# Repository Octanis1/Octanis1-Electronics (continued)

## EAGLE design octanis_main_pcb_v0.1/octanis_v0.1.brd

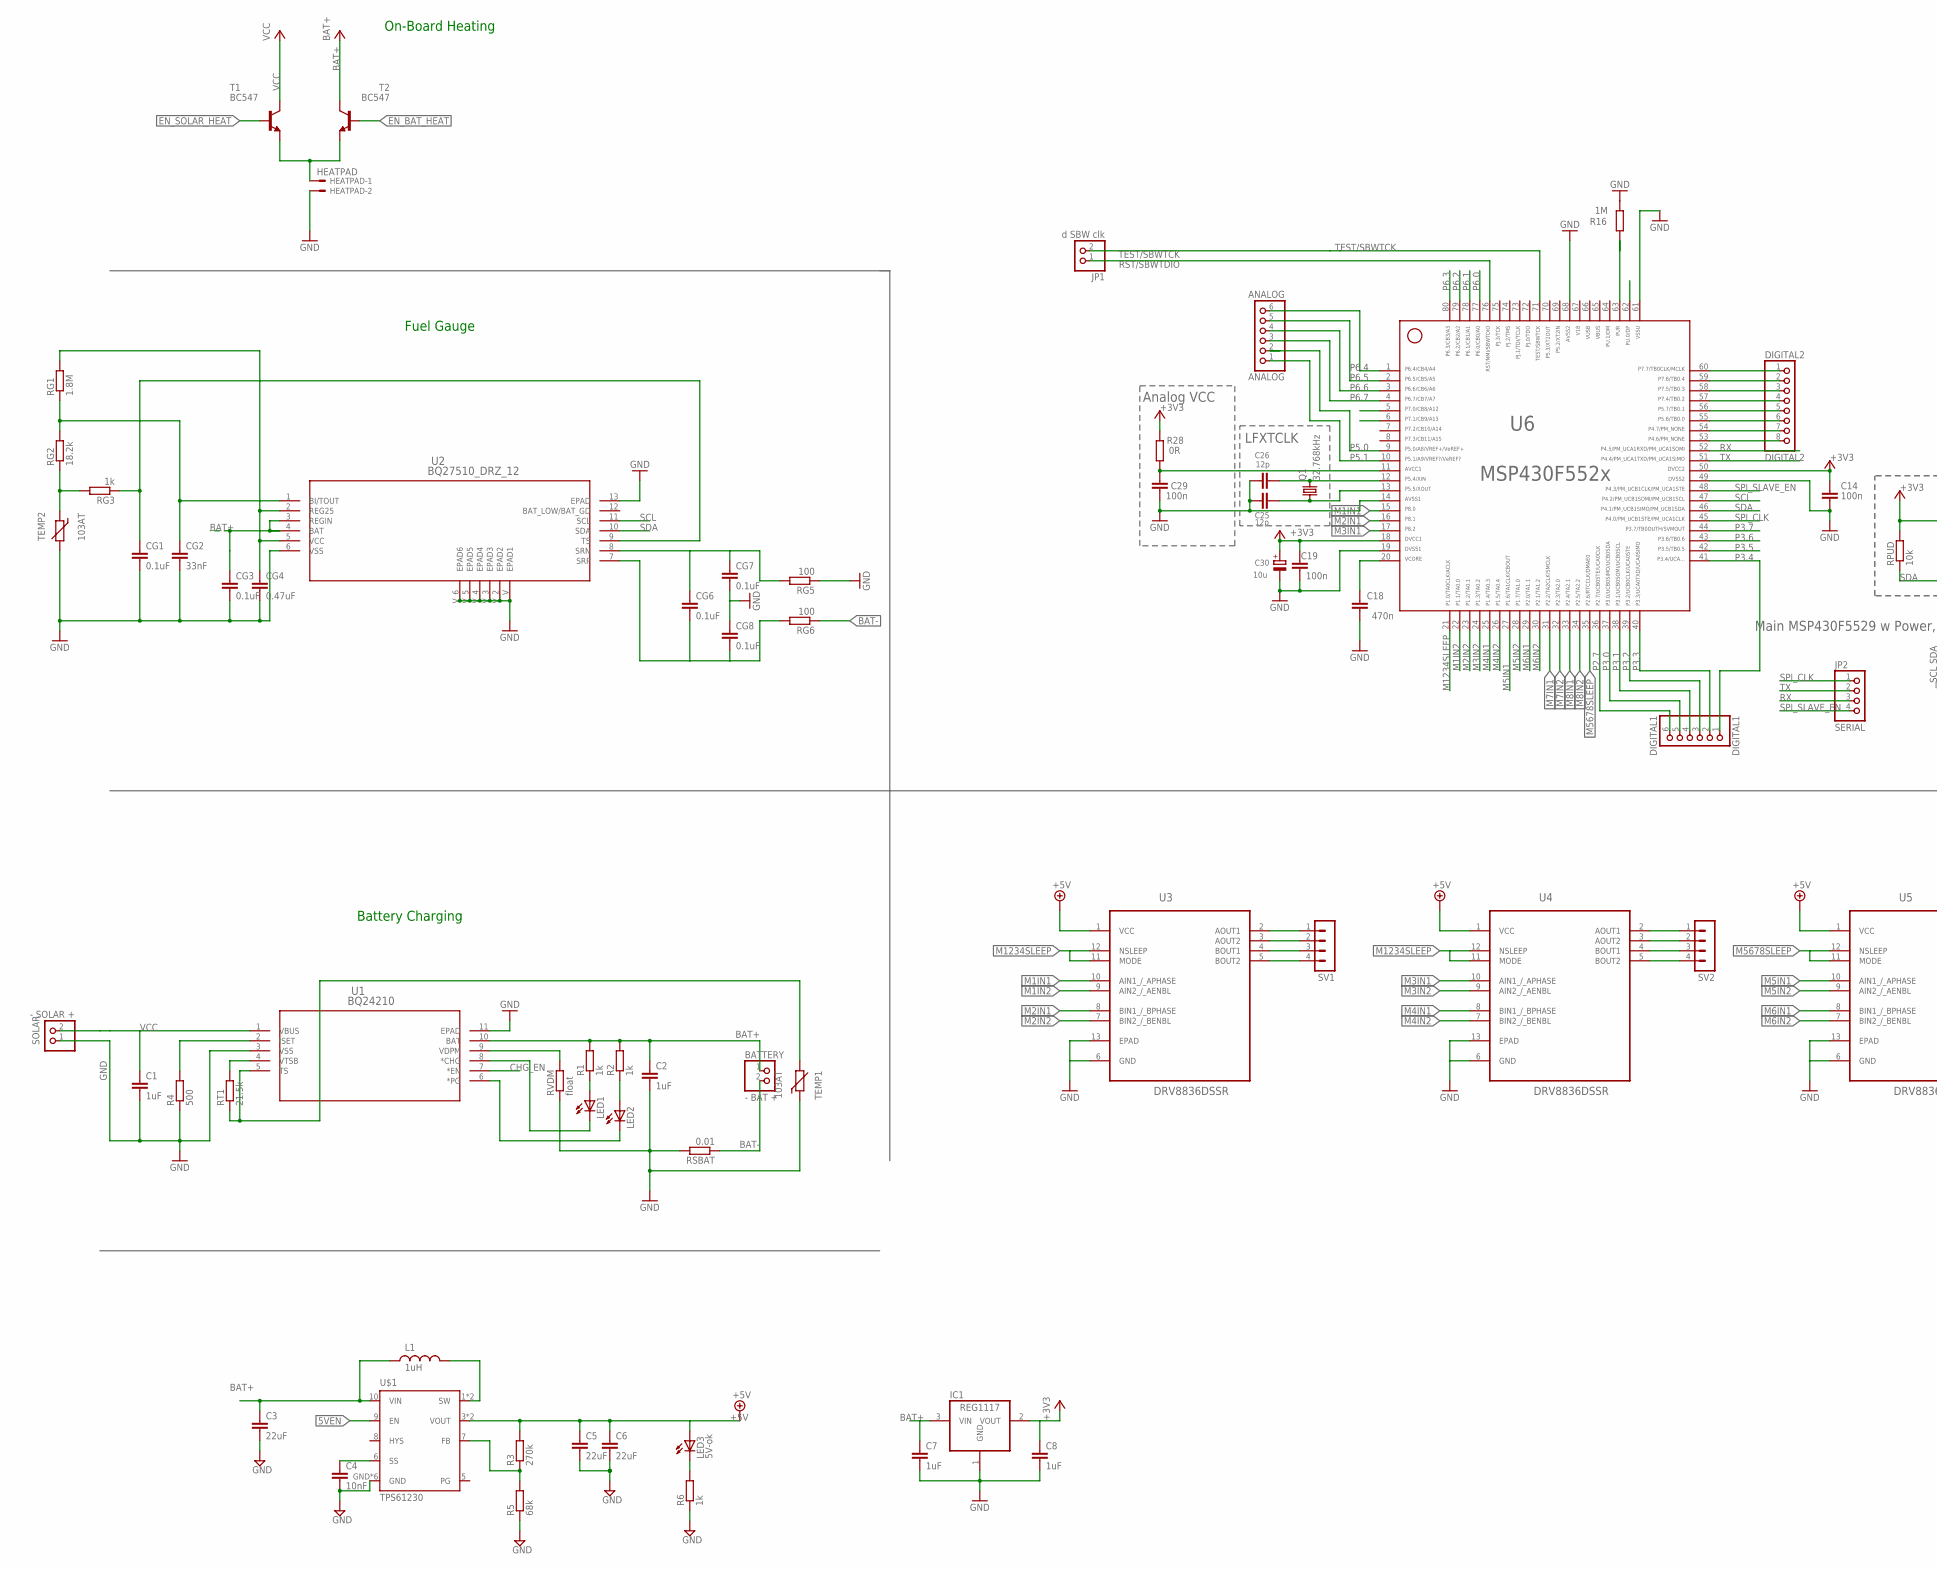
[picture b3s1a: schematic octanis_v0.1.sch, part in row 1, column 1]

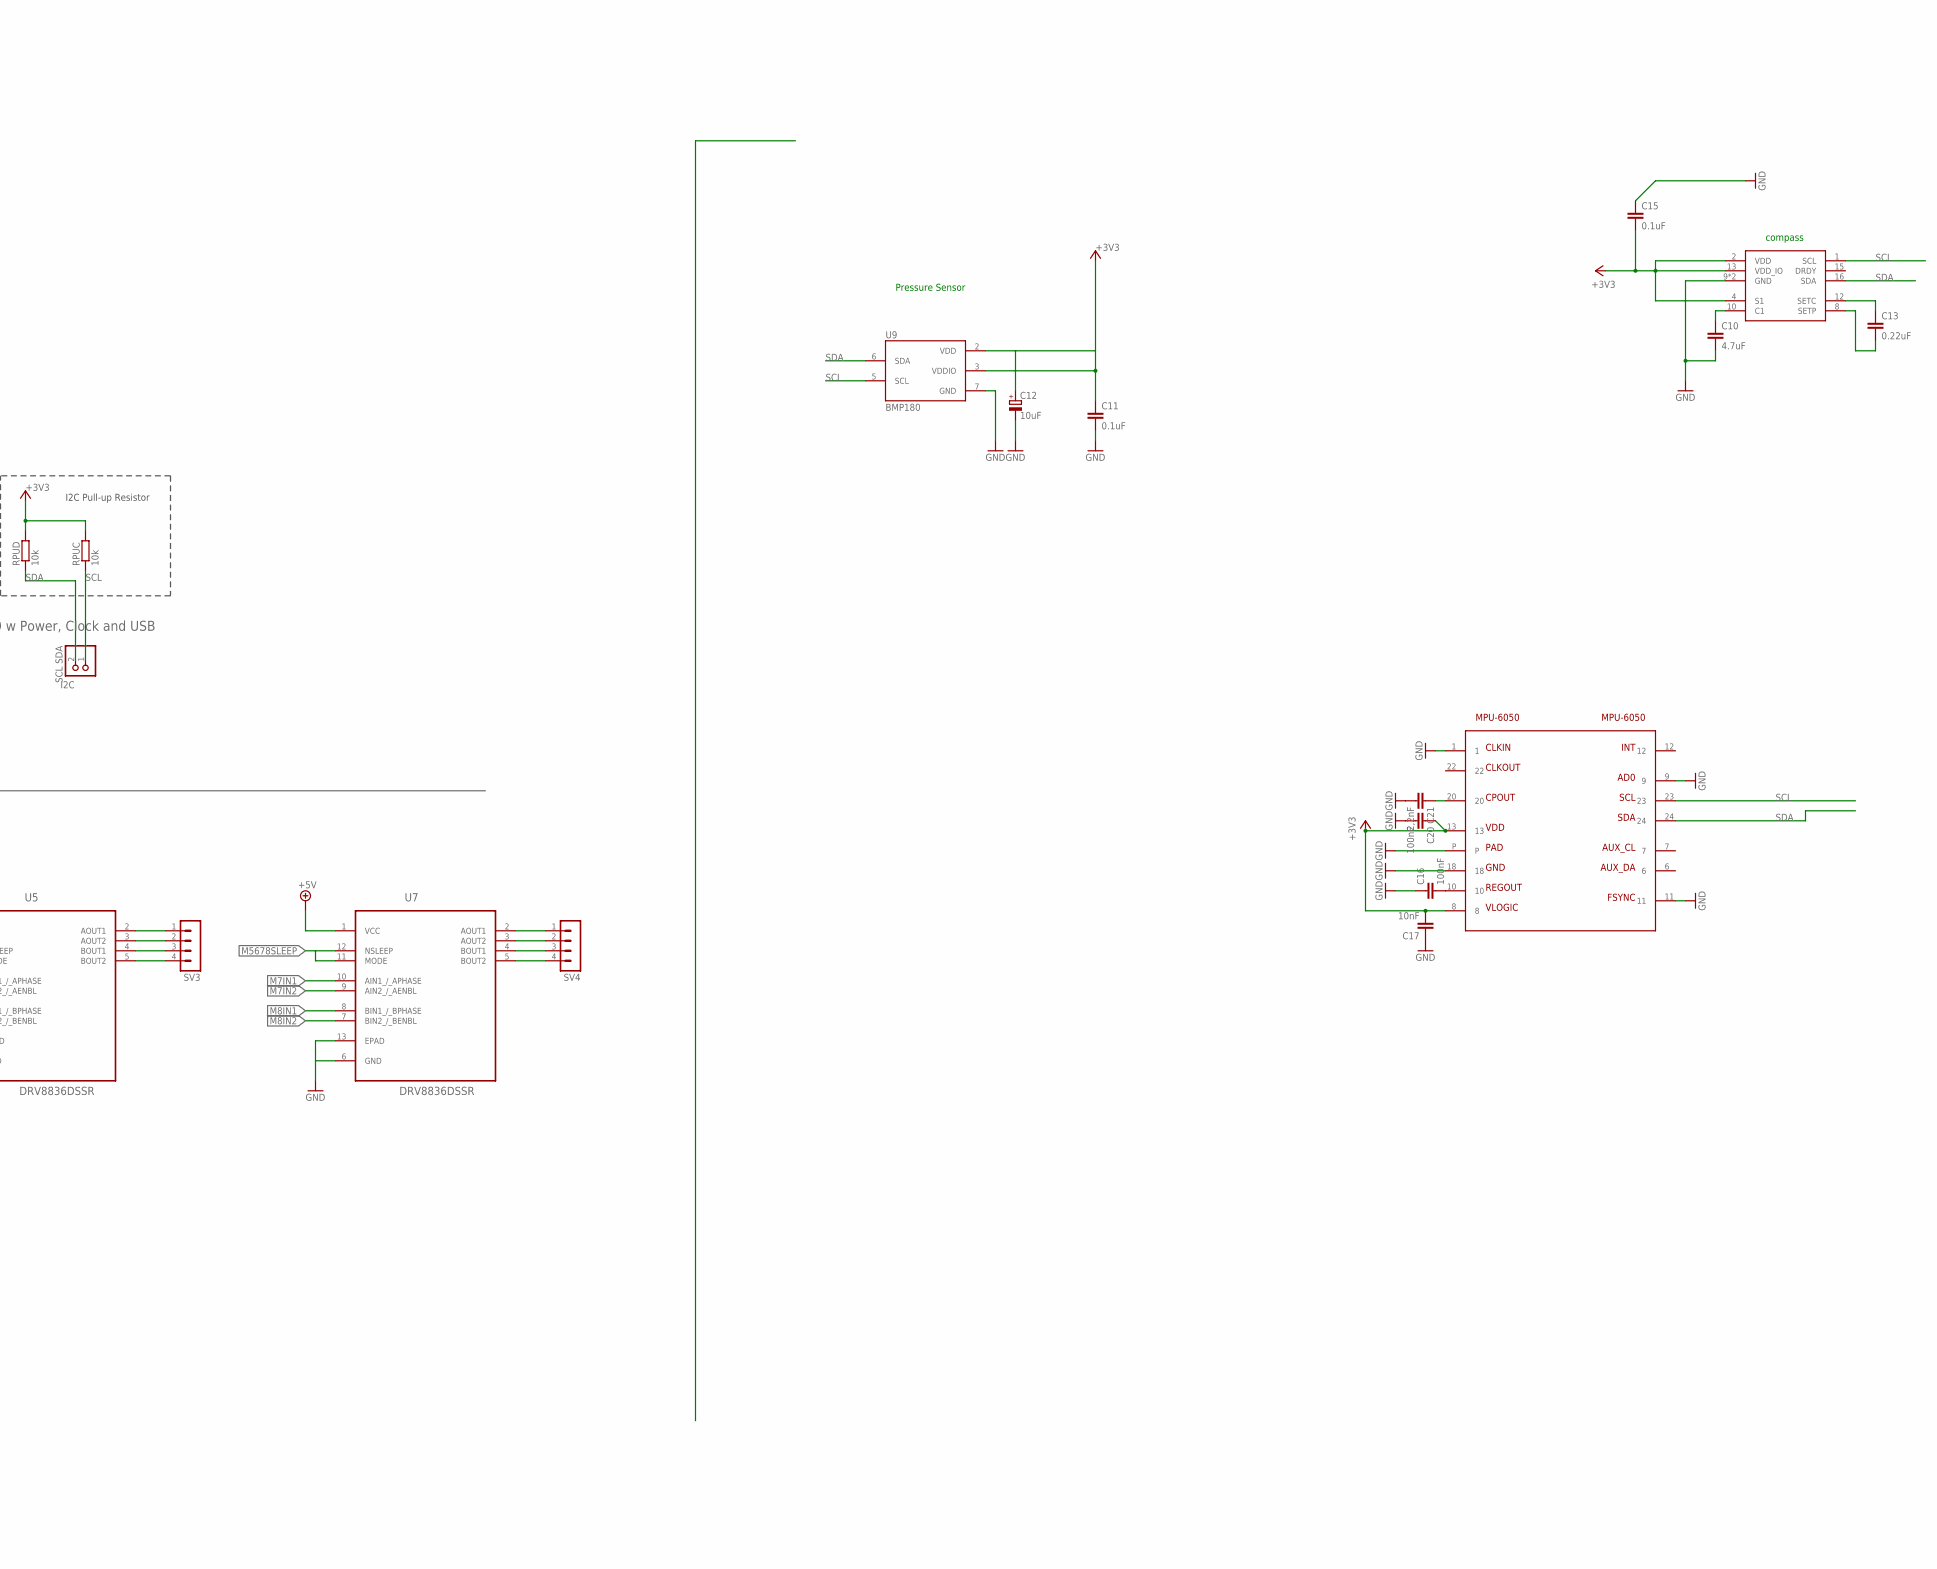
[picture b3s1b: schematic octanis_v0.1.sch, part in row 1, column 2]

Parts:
ANALOG: ANALOG; 1X06
BATTERY: - BAT +; 1X02
C1, C2: 1uF; C1206
C3, C5, C6: 22uF; C0603
C4, C17: 10nF; C0603
C7, C8: 1uF; C0603
C10: 4.7uF; C0603
C11, C15: 0.1uF; C0603
C12: 10uF; A/3216-18R
C13: 0.22uF; C0603
C14, C19, C29: 100n; C0603
C16, C20: 100nF; C0603
C18: 470n; C0603
C21: 2,2nF; C0603
C25, C26: 12p; C0603
C30: 10u; A/3216-18R
CG1, CG3, CG6, CG7, CG8: 0.1uF; C0603
CG2: 33nF; C0603
CG4: 0.47uF; C0603
COMPASS: HMC5883L; LPCC16
DIGITAL1: DIGITAL1; 1X06
DIGITAL2: DIGITAL2; 1X08
HEATPAD: HEATPAD; 22-23-2021
I2C: SCL SDA; 1X02
IC1: REG1117; SOT223
JP1: d SBW clk; 1X02
JP2: SERIAL; 1X04
L1: 1uH; XFL4020
LED1, LED2: LEDCHIP-LED0603; CHIP-LED0603
LED3: 5V-ok; CHIPLED_0603
MPU-6050: MPU-6050; QFN24
Q1: 32.768kHz; FC-12M
R1, R2, R6: 1k; R0603
R3: 270k; R0603
R4: 500; R1206
R5: 68k; R0603
R16: 1M; R0603
R28: 0R; R0603
RG1: 1.8M; R0603
RG2: 18.2k; R0603
RG3: 1k; R0603
RG5, RG6: 100; R0603
RPUC: 10k; R0603
RPUD: 10k; R0603
RSBAT: 0.01; R1206
RT1: 21.5k; R1206
RVDM: float; R1206
SOLAR: - SOLAR +; 1X02
SV1, SV2, SV3, SV4: MA04-1
T1, T2: BC547; TO92
TEMP1, TEMP2: 103AT; RS-2,5
U1: BQ24210; DQC10_P84X2P4
U2: BQ27510_DRZ_12; DRZ12_1P95X2P45
U3, U4, U5, U7: DRV8836DSSR; SON50P200X300X80-13N
U6: MSP430F5529IPNR; PN80
U9: BMP180
U$1: TPS61230; DRC-S-PVSON-N11

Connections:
5VEN: U6.6, U$1.9 (EN)
65: U6.65
66: U6.66
67: U6.67
+3V3: C8.1, C11.1, C12.+, C14.1, C15.2, C17.2, C19.2, C20.1, C30.+, COMPASS.2 (VDD), COMPASS.4 (S1), COMPASS.13 (VDD_IO), IC1.2 (VOUT), MPU-6050.8, MPU-6050.13, R28.2, RPUC.2, RPUD.2, U6.18, U6.50, U9.2 (VDD), U9.3 (VDDIO)
+5V: C5.1, C6.1, LED3.A, R3.2, U3.1 (VCC), U4.1 (VCC), U5.1 (VCC), U7.1 (VCC), U$1.3 (VOUT), U$1.4 (VOUT)
AVCC: C29.1, R28.1, U6.11
BAT+: BATTERY.1, C2.1, C3.1, C7.1, CG3.1, IC1.3 (VIN), L1.P$1 (1), R1.2, R2.2, T2.3 (C), U1.10 (BAT), U2.3 (REGIN), U2.4 (BAT), U$1.10 (VIN)
BAT-: BATTERY.2, RG6.1, RSBAT.1
CHG_EN: U1.7 (*EN), U6.5
EN_BAT_HEAT: T2.2 (B)
EN_SOLAR_HEAT: T1.2 (B)
GND: C1.2, C2.2, C3.2, C4.2, C5.2, C6.2, C7.2, C8.2, C10.2, C11.2, C12.-, C14.2, C15.1, C16.1, C17.1, C18.1, C19.1, C20.2, C21.2, C25.1, C26.1, C29.2, C30.-, CG1.2, CG2.2, CG3.2, CG4.2, CG7.2, CG8.1, COMPASS.9 (GND), COMPASS.11 (GND), HEATPAD.2, IC1.1 (GND), MPU-6050.1, MPU-6050.9, MPU-6050.11, MPU-6050.18, MPU-6050.P, R4.1, R5.1, R6.1, R16.1, RG5.1, RSBAT.2, RVDM.1, SOLAR.1, TEMP1.1, TEMP2.2, U1.3 (VSS), U1.11 (EPAD), U2.6 (VSS), U2.13 (EPAD), U2.V (EPAD1), U2.V_2 (EPAD2), U2.V_3 (EPAD3), U2.V_4 (EPAD4), U2.V_5 (EPAD5), U2.V_6 (EPAD6), U3.6 (GND), U3.13 (EPAD), U4.6 (GND), U4.13 (EPAD), U5.6 (GND), U5.13 (EPAD), U6.14, U6.19, U6.49, U6.61, U6.68, U7.6 (GND), U7.13 (EPAD), U9.7 (GND), U$1.GND, U$1.GND@1 (GND), U$1.GND@2 (GND), U$1.GND@3 (GND), U$1.GND@4 (GND), U$1.GND@5 (GND)
IND: L1.P$2 (2), U$1.1 (SW), U$1.2 (SW)
M1IN1: U3.10 (AIN1_/_APHASE), U6.15
M1IN2: U3.9 (AIN2_/_AENBL), U6.22
M2IN1: U3.8 (BIN1_/_BPHASE), U6.16
M2IN2: U3.7 (BIN2_/_BENBL), U6.23
M3IN1: U4.10 (AIN1_/_APHASE), U6.17
M3IN2: U4.9 (AIN2_/_AENBL), U6.24
M4IN1: U4.8 (BIN1_/_BPHASE), U6.25
M4IN2: U4.7 (BIN2_/_BENBL), U6.26
M5IN1: U5.10 (AIN1_/_APHASE), U6.27
M5IN2: U5.9 (AIN2_/_AENBL), U6.28
M6IN1: U5.8 (BIN1_/_BPHASE), U6.29
M6IN2: U5.7 (BIN2_/_BENBL), U6.30
M7IN1: U6.31, U7.10 (AIN1_/_APHASE)
M7IN2: U6.32, U7.9 (AIN2_/_AENBL)
M8IN1: U6.33, U7.8 (BIN1_/_BPHASE)
M8IN2: U6.34, U7.7 (BIN2_/_BENBL)
M1234SLEEP: U3.11 (MODE), U3.12 (NSLEEP), U4.11 (MODE), U4.12 (NSLEEP), U6.21
M5678SLEEP: U5.11 (MODE), U5.12 (NSLEEP), U6.35, U7.11 (MODE), U7.12 (NSLEEP)
unnamed: CG2.1, RG1.1, RG2.2, U2.1 (BI/TOUT)
unnamed: LED1.A, R1.1
unnamed: LED2.A, R2.1
unnamed: LED1.C, U1.8 (*CHG)
unnamed: LED2.C, U1.6 (*PG)
unnamed: RVDM.2, U1.9 (VDPM)
unnamed: RT1.1, TEMP1.2, U1.5 (TS)
unnamed: RT1.2, U1.4 (VTSB)
unnamed: R4.2, U1.2 (ISET)
unnamed: SV2.1, U4.2 (AOUT1)
unnamed: DIGITAL2.1, U6.60
unnamed: DIGITAL2.2, U6.59
unnamed: C10.1, COMPASS.10 (C1)
unnamed: C16.2, MPU-6050.10
unnamed: C21.1, MPU-6050.20
unnamed: DIGITAL2.3, U6.58
unnamed: DIGITAL2.4, U6.57
unnamed: DIGITAL2.5, U6.56
unnamed: DIGITAL2.6, U6.55
unnamed: DIGITAL2.7, U6.54
unnamed: C13.2, COMPASS.8 (SETP)
unnamed: DIGITAL2.8, U6.53
unnamed: C13.1, COMPASS.12 (SETC)
unnamed: RG2.1, RG3.2, TEMP2.1
unnamed: CG1.1, RG3.1, U2.9 (TS)
unnamed: CG4.1, RG1.2, U2.2 (REG25), U2.5 (VCC)
unnamed: CG6.1, CG7.1, RG5.2, U2.8 (SRN)
unnamed: HEATPAD.1, T1.1 (E), T2.1 (E)
unnamed: CG6.2, CG8.2, RG6.2, U2.7 (SRP)
unnamed: SV2.2, U4.3 (AOUT2)
unnamed: SV2.3, U4.4 (BOUT1)
unnamed: SV2.4, U4.5 (BOUT2)
unnamed: C4.1, U$1.6 (SS)
unnamed: R3.1, R5.2, U$1.7 (FB)
unnamed: LED3.C, R6.2
unnamed: SV3.1, U5.2 (AOUT1)
unnamed: SV3.2, U5.3 (AOUT2)
unnamed: SV3.3, U5.4 (BOUT1)
unnamed: SV3.4, U5.5 (BOUT2)
unnamed: SV1.1, U3.2 (AOUT1)
unnamed: SV1.2, U3.3 (AOUT2)
unnamed: SV1.3, U3.4 (BOUT1)
unnamed: SV1.4, U3.5 (BOUT2)
unnamed: SV4.1, U7.2 (AOUT1)
unnamed: SV4.2, U7.3 (AOUT2)
unnamed: SV4.3, U7.4 (BOUT1)
unnamed: SV4.4, U7.5 (BOUT2)
P2.7: DIGITAL1.6, U6.36
P3.0: DIGITAL1.5, U6.37
P3.1: DIGITAL1.4, U6.38
P3.2: DIGITAL1.3, U6.39
P3.3: DIGITAL1.2, U6.40
P3.4: DIGITAL1.1, U6.41
P3.5: U6.42
P3.6: U6.43
P3.7: U6.44
P5.0: ANALOG.2, U6.9
P5.1: ANALOG.1, U6.10
P5.4/XIN: C26.2, Q1.2, U6.12
P5.5/XOUT: C25.2, Q1.1, U6.13
P6.0: U6.77
P6.1: U6.78
P6.2: U6.79
P6.3: U6.80
P6.4: ANALOG.6, U6.1
P6.5: ANALOG.5, U6.2
P6.6: ANALOG.4, U6.3
P6.7: ANALOG.3, U6.4
PG: U$1.5 (PG)
RST/SBWTDIO: JP1.1, U6.76
RX: JP2.3, U6.52
SCL: COMPASS.1 (SCL), I2C.1, MPU-6050.23, RPUC.1, U2.11 (SCL), U6.47, U9.5 (SCL)
SDA: COMPASS.16 (SDA), I2C.2, MPU-6050.24, RPUD.1, U2.10 (SDA), U6.46, U9.6 (SDA)
SPI_CLK: JP2.1, U6.45
SPI_SLAVE_EN: JP2.4, U6.48
TARGET_DP: U6.62
TARGET_PUR: R16.2, U6.63
TEST/SBWTCK: JP1.2, U6.71
TX: JP2.2, U6.51
VCC: C1.1, SOLAR.2, T1.3 (C), U1.1 (VBUS)
VCORE: C18.2, U6.20

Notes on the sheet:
Battery Charging
Fuel Gauge
LFXTCLK
Main MSP430F5529 w Power, Clock and USB
Analog VCC
I2C Pull-up Resistor
On-Board Heating
Pressure Sensor
compass

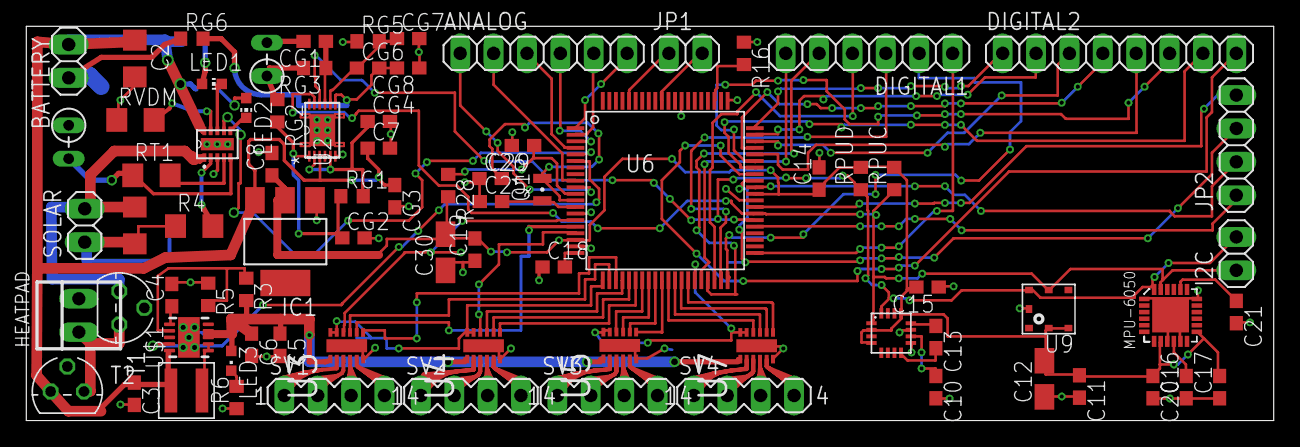
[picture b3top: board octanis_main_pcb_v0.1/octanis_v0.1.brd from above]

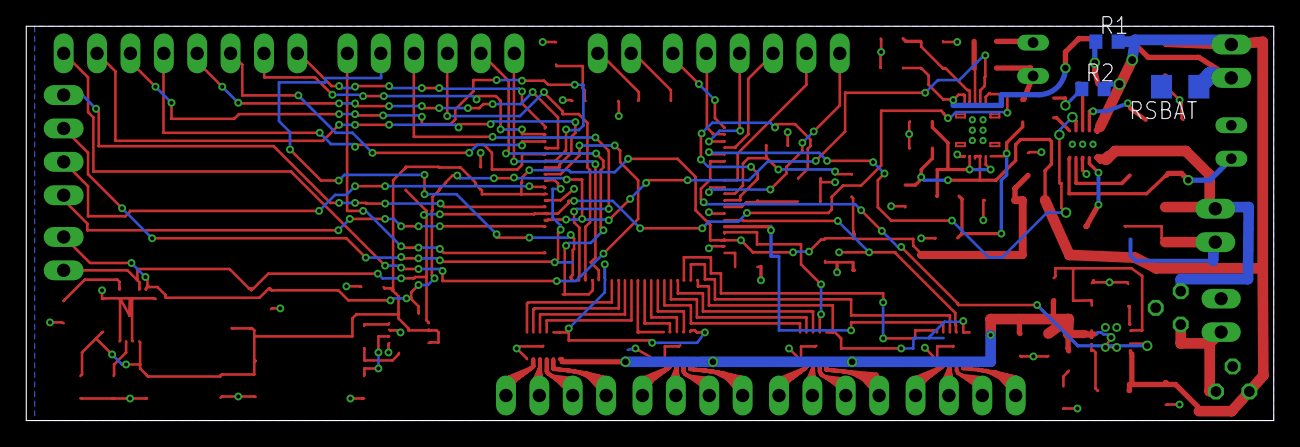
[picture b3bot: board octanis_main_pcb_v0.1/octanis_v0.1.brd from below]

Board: 4 copper layers, 94.9 x 30.0 mm, 83 parts (3 on the bottom side), 99 nets.

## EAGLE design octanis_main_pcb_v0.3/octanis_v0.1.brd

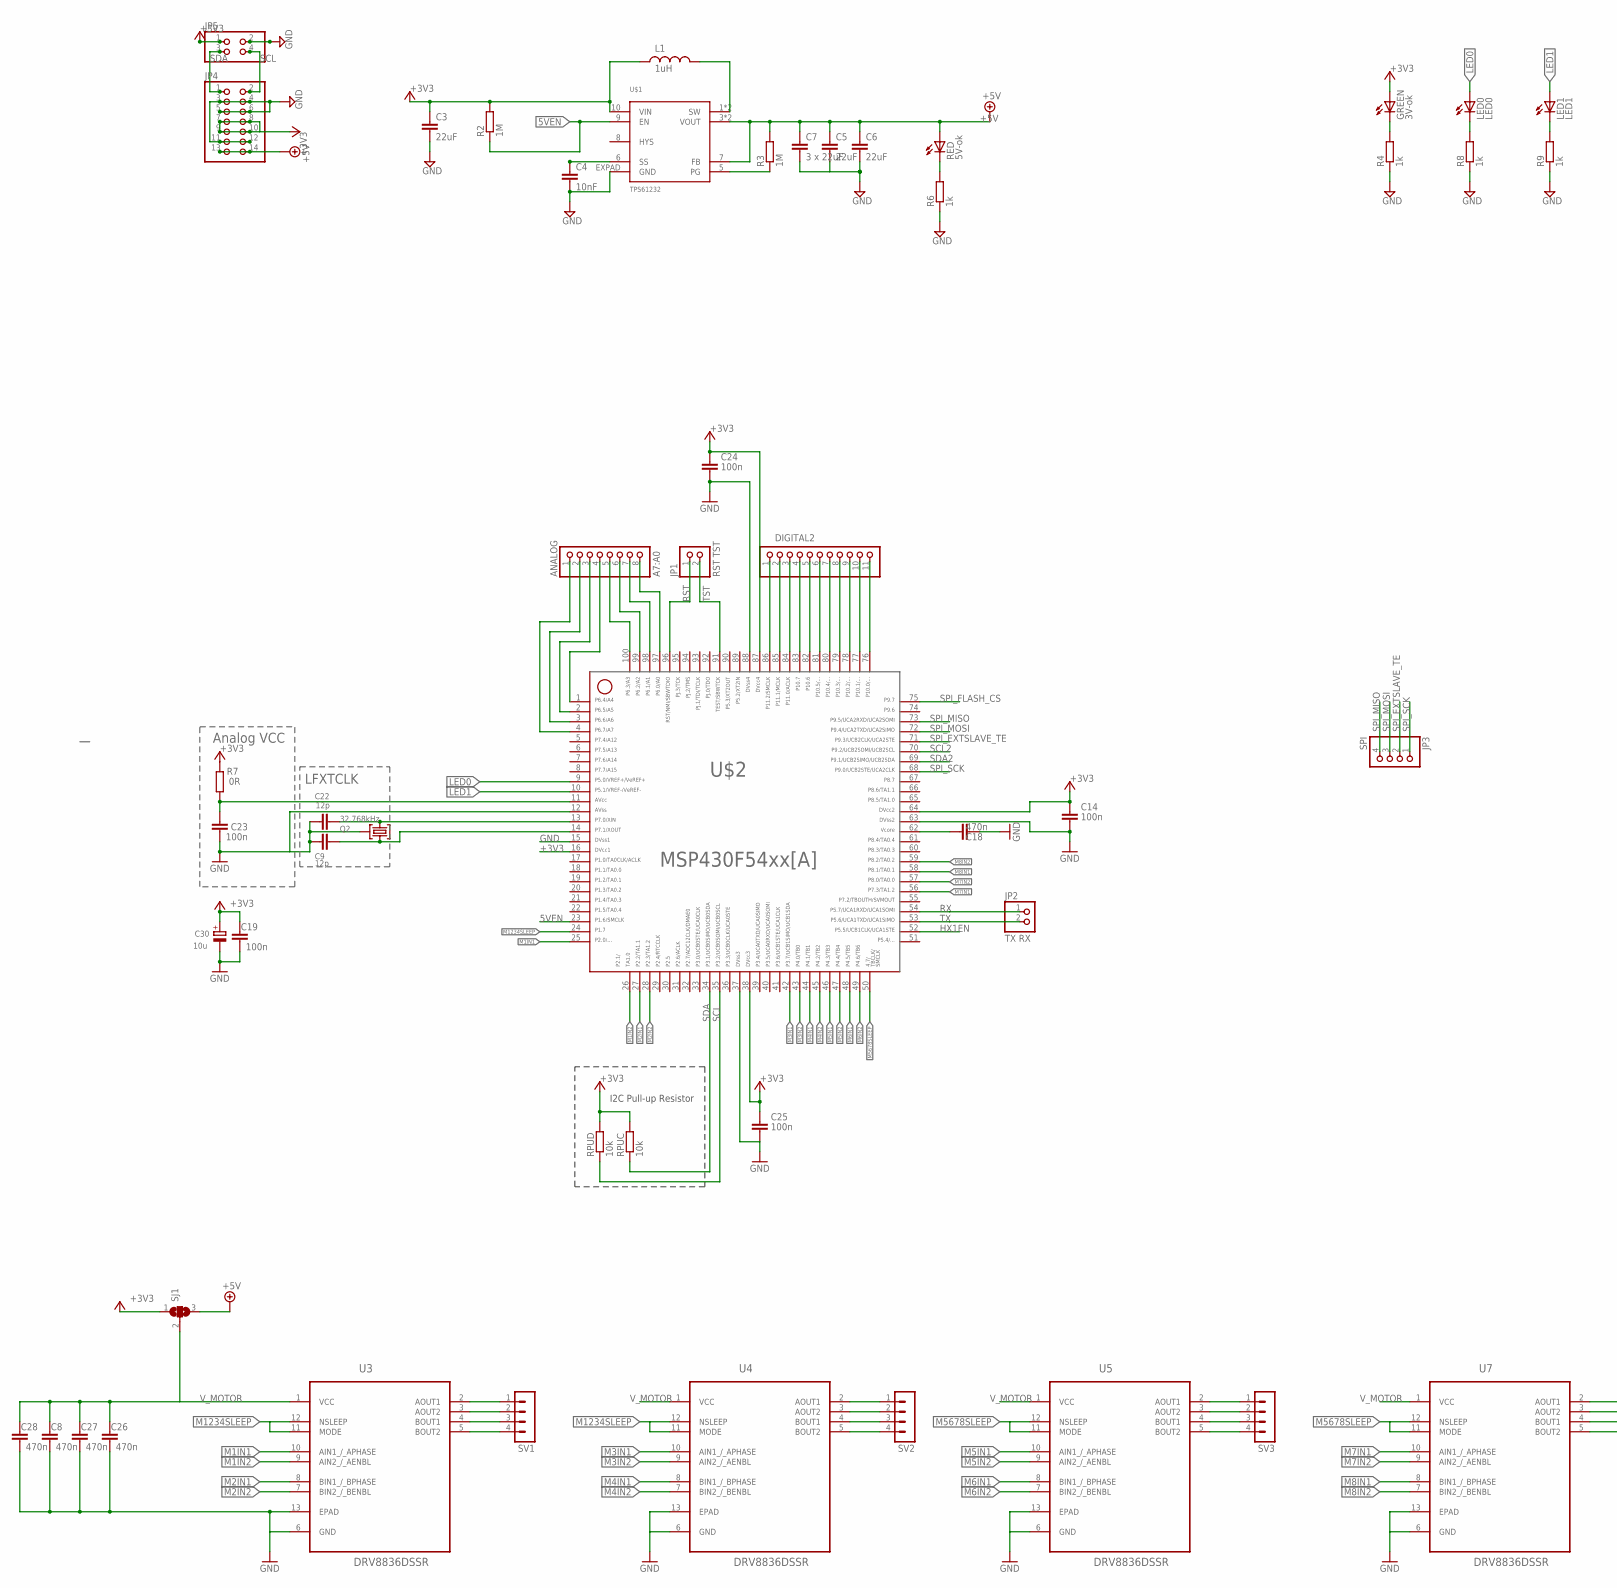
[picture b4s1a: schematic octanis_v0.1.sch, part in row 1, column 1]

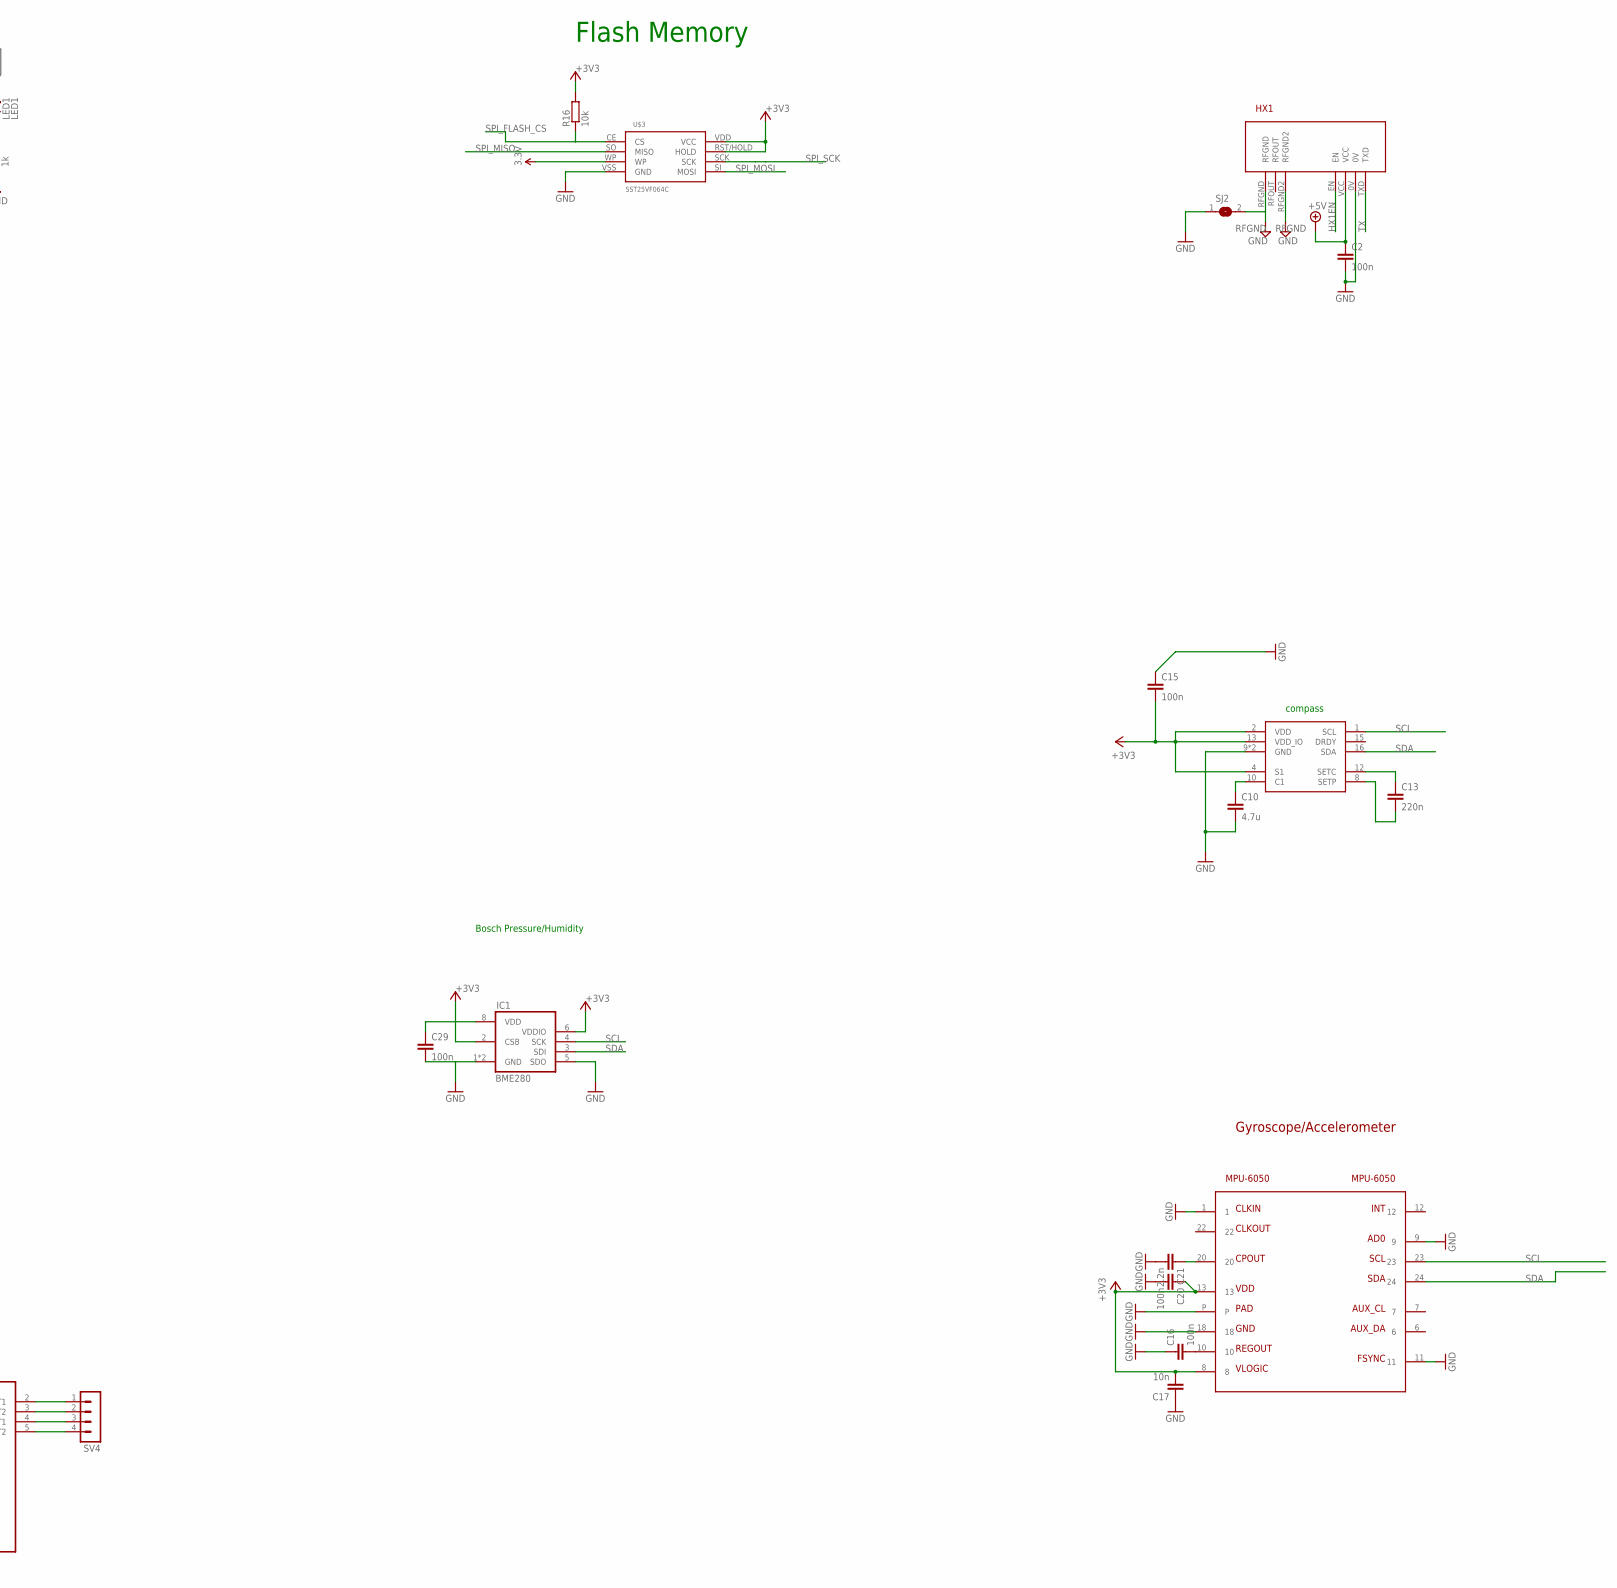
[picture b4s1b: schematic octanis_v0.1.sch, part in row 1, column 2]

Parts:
ANALOG: A7:A0; 1X08
C2, C14, C15, C16, C19, C20, C24, C25, C29: 100n; C0603
C3, C5, C6: 22uF; C0603
C4: 10nF; C0603
C7: 3 x 22uF; C0603
C8, C18, C26, C27, C28: 470n; C0603
C9, C22: 12p; C0402
C10: 4.7u; C0603
C13: 220n; C0603
C17: 10n; C0603
C21: 2.2n; C0603
C23: 100n; C0402
C30: 10u; A/3216-18R
COMPASS: HMC5883L; LPCC16
DIGITAL2: DIGITAL I/O; 1X11
GREEN: 3V-ok; CHIPLED_0603
IC1: BME280
JP1: RST TST; 1X02
JP2: TX RX; 1X02
JP3: SPI; 1X04
JP4: PINHD-2X7; 2X07
JP5: PINHD-2X2; 2X02
L1: 1uH; XFL4020
LED0: LED0; CHIPLED_0603
LED1: LED1; CHIPLED_0603
MPU-6050: MPU-6050; QFN24
Q2: 32.768kHz; MS3V-T1R
R2, R3: 1M; R0603
R4, R6, R8, R9: 1k; R0603
R7: 0R; R0402
R16: 10k; R0603
RED: 5V-ok; CHIPLED_0603
RPUC: 10k; R0603
RPUD: 10k; R0603
SJ1: SJ2W; SJ_2
SJ2: SJ
SV1, SV2, SV3, SV4: MA04-1
U3, U4, U5, U7: DRV8836DSSR; SON50P200X300X80-13N
U$1: TPS61232; S-PVSON-N10
U$2: MSP430F5438A; PZ100
U$3: SST25VF064C; SOIC_8-LEAD
U$4: HX1

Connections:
3.3V: U$3.WP
5VEN: R2.1, U$1.9 (EN), U$2.23
+3V3: C3.1, C14.1, C15.2, C17.2, C19.2, C20.1, C24.1, C25.1, C29.1, C30.+, COMPASS.2 (VDD), COMPASS.4 (S1), COMPASS.13 (VDD_IO), GREEN.A, IC1.2 (CSB), IC1.6 (VDDIO), IC1.8 (VDD), JP4.7, JP4.8, JP4.9, JP4.10, JP5.1, L1.P$1 (1), MPU-6050.8, MPU-6050.13, R2.2, R7.2, R16.2, RPUC.2, RPUD.2, SJ1.1, U$1.10 (VIN), U$2.16, U$2.38, U$2.64, U$2.87, U$3.RST/HOLD (HOLD), U$3.VDD (VCC)
+5V: C2.1, C5.1, C6.1, C7.1, JP4.13, JP4.14, R3.2, RED.A, SJ1.3, U$1.3 (VOUT), U$1.4 (VOUT), U$1.7 (FB), U$4.VCC
AVCC1: C23.1, R7.1, U$2.11
GND: C2.2, C3.2, C4.2, C5.2, C6.2, C7.2, C8.1, C9.1, C10.2, C14.2, C15.1, C16.1, C17.1, C18.1, C19.1, C20.2, C21.2, C22.1, C23.2, C24.2, C25.2, C26.1, C27.1, C28.1, C29.2, C30.-, COMPASS.9 (GND), COMPASS.11 (GND), IC1.1 (GND), IC1.5 (SDO), IC1.7 (GND), JP4.3, JP4.4, JP4.5, JP4.6, JP4.11, JP4.12, JP5.2, MPU-6050.1, MPU-6050.9, MPU-6050.11, MPU-6050.18, MPU-6050.P, Q2.P3 (GND), R4.1, R6.1, R8.1, R9.1, SJ2.1, U3.6 (GND), U3.13 (EPAD), U4.6 (GND), U4.13 (EPAD), U5.6 (GND), U5.13 (EPAD), U7.6 (GND), U7.13 (EPAD), U$1.EXPAD (GND), U$2.12, U$2.15, U$2.37, U$2.63, U$2.88, U$3.VSS (GND), U$4.0V
HX1EN: U$2.52, U$4.EN
IND: L1.P$2 (2), U$1.1 (SW), U$1.2 (SW)
LED0: LED0.A, U$2.9
LED1: LED1.A, U$2.10
M1IN1: U3.10 (AIN1_/_APHASE), U$2.25
M1IN2: U3.9 (AIN2_/_AENBL), U$2.26
M2IN1: U3.8 (BIN1_/_BPHASE), U$2.27
M2IN2: U3.7 (BIN2_/_BENBL), U$2.28
M3IN1: U4.10 (AIN1_/_APHASE), U$2.42
M3IN2: U4.9 (AIN2_/_AENBL), U$2.43
M4IN1: U4.8 (BIN1_/_BPHASE), U$2.44
M4IN2: U4.7 (BIN2_/_BENBL), U$2.45
M5IN1: U5.10 (AIN1_/_APHASE), U$2.46
M5IN2: U5.9 (AIN2_/_AENBL), U$2.47
M6IN1: U5.8 (BIN1_/_BPHASE), U$2.48
M6IN2: U5.7 (BIN2_/_BENBL), U$2.49
M7IN1: U7.10 (AIN1_/_APHASE), U$2.56
M7IN2: U7.9 (AIN2_/_AENBL), U$2.57
M8IN1: U7.8 (BIN1_/_BPHASE), U$2.58
M8IN2: U7.7 (BIN2_/_BENBL), U$2.59
M1234SLEEP: U3.11 (MODE), U3.12 (NSLEEP), U4.11 (MODE), U4.12 (NSLEEP), U$2.24
M5678SLEEP: U5.11 (MODE), U5.12 (NSLEEP), U7.11 (MODE), U7.12 (NSLEEP), U$2.50
unnamed: R3.1, U$1.5 (PG)
unnamed: GREEN.C, R4.2
unnamed: LED0.C, R8.2
unnamed: LED1.C, R9.2
unnamed: SV2.1, U4.2 (AOUT1)
unnamed: DIGITAL2.1, U$2.86
unnamed: DIGITAL2.2, U$2.85
unnamed: C10.1, COMPASS.10 (C1)
unnamed: C16.2, MPU-6050.10
unnamed: C21.1, MPU-6050.20
unnamed: DIGITAL2.3, U$2.84
unnamed: DIGITAL2.4, U$2.83
unnamed: DIGITAL2.5, U$2.82
unnamed: DIGITAL2.6, U$2.81
unnamed: DIGITAL2.7, U$2.80
unnamed: C13.2, COMPASS.8 (SETP)
unnamed: DIGITAL2.8, U$2.79
unnamed: ANALOG.8, U$2.97
unnamed: ANALOG.7, U$2.98
unnamed: ANALOG.6, U$2.99
unnamed: DIGITAL2.9, U$2.78
unnamed: C13.1, COMPASS.12 (SETC)
unnamed: SV2.2, U4.3 (AOUT2)
unnamed: SV2.3, U4.4 (BOUT1)
unnamed: SV2.4, U4.5 (BOUT2)
unnamed: C4.1, U$1.6 (SS)
unnamed: R6.2, RED.C
unnamed: SV3.1, U5.2 (AOUT1)
unnamed: SV3.2, U5.3 (AOUT2)
unnamed: SV3.3, U5.4 (BOUT1)
unnamed: SV3.4, U5.5 (BOUT2)
unnamed: SV1.1, U3.2 (AOUT1)
unnamed: SV1.2, U3.3 (AOUT2)
unnamed: SV1.3, U3.4 (BOUT1)
unnamed: SV1.4, U3.5 (BOUT2)
unnamed: SV4.1, U7.2 (AOUT1)
unnamed: SV4.2, U7.3 (AOUT2)
unnamed: SV4.3, U7.4 (BOUT1)
unnamed: SV4.4, U7.5 (BOUT2)
unnamed: ANALOG.5, U$2.100
unnamed: ANALOG.4, U$2.1
unnamed: ANALOG.3, U$2.2
unnamed: ANALOG.2, U$2.3
unnamed: ANALOG.1, U$2.4
unnamed: DIGITAL2.10, U$2.77
unnamed: DIGITAL2.11, U$2.76
P5.4/XIN1: C22.2, Q2.P2 (2), U$2.13
P5.5/XOUT1: C9.2, Q2.P1 (1), U$2.14
RFGND: SJ2.2, U$4.RFGND, U$4.RFGND2
RST: JP1.1, U$2.96
RX: JP2.1, U$2.54
SCL: COMPASS.1 (SCL), IC1.4 (SCK), JP4.2, JP5.4, MPU-6050.23, RPUD.1, U$2.35
SCL2: U$2.70
SDA: COMPASS.16 (SDA), IC1.3 (SDI), JP4.1, JP5.3, MPU-6050.24, RPUC.1, U$2.34
SDA2: U$2.69
SPI_EXTSLAVE_TE: JP3.2, U$2.71
SPI_FLASH_CS: R16.1, U$2.75, U$3.CE (CS)
SPI_MISO: JP3.4, U$2.73, U$3.SO (MISO)
SPI_MOSI: JP3.3, U$2.72, U$3.SI (MOSI)
SPI_SCK: JP3.1, U$2.68, U$3.SCK
TST: JP1.2, U$2.91
TX: JP2.2, U$2.53, U$4.TXD
VCORE: C18.2, U$2.62
V_MOTOR: C8.2, C26.2, C27.2, C28.2, SJ1.2, U3.1 (VCC), U4.1 (VCC), U5.1 (VCC), U7.1 (VCC)

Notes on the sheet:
compass
LFXTCLK
Analog VCC
I2C Pull-up Resistor
Flash Memory
Gyroscope/Accelerometer
Bosch Pressure/Humidity
